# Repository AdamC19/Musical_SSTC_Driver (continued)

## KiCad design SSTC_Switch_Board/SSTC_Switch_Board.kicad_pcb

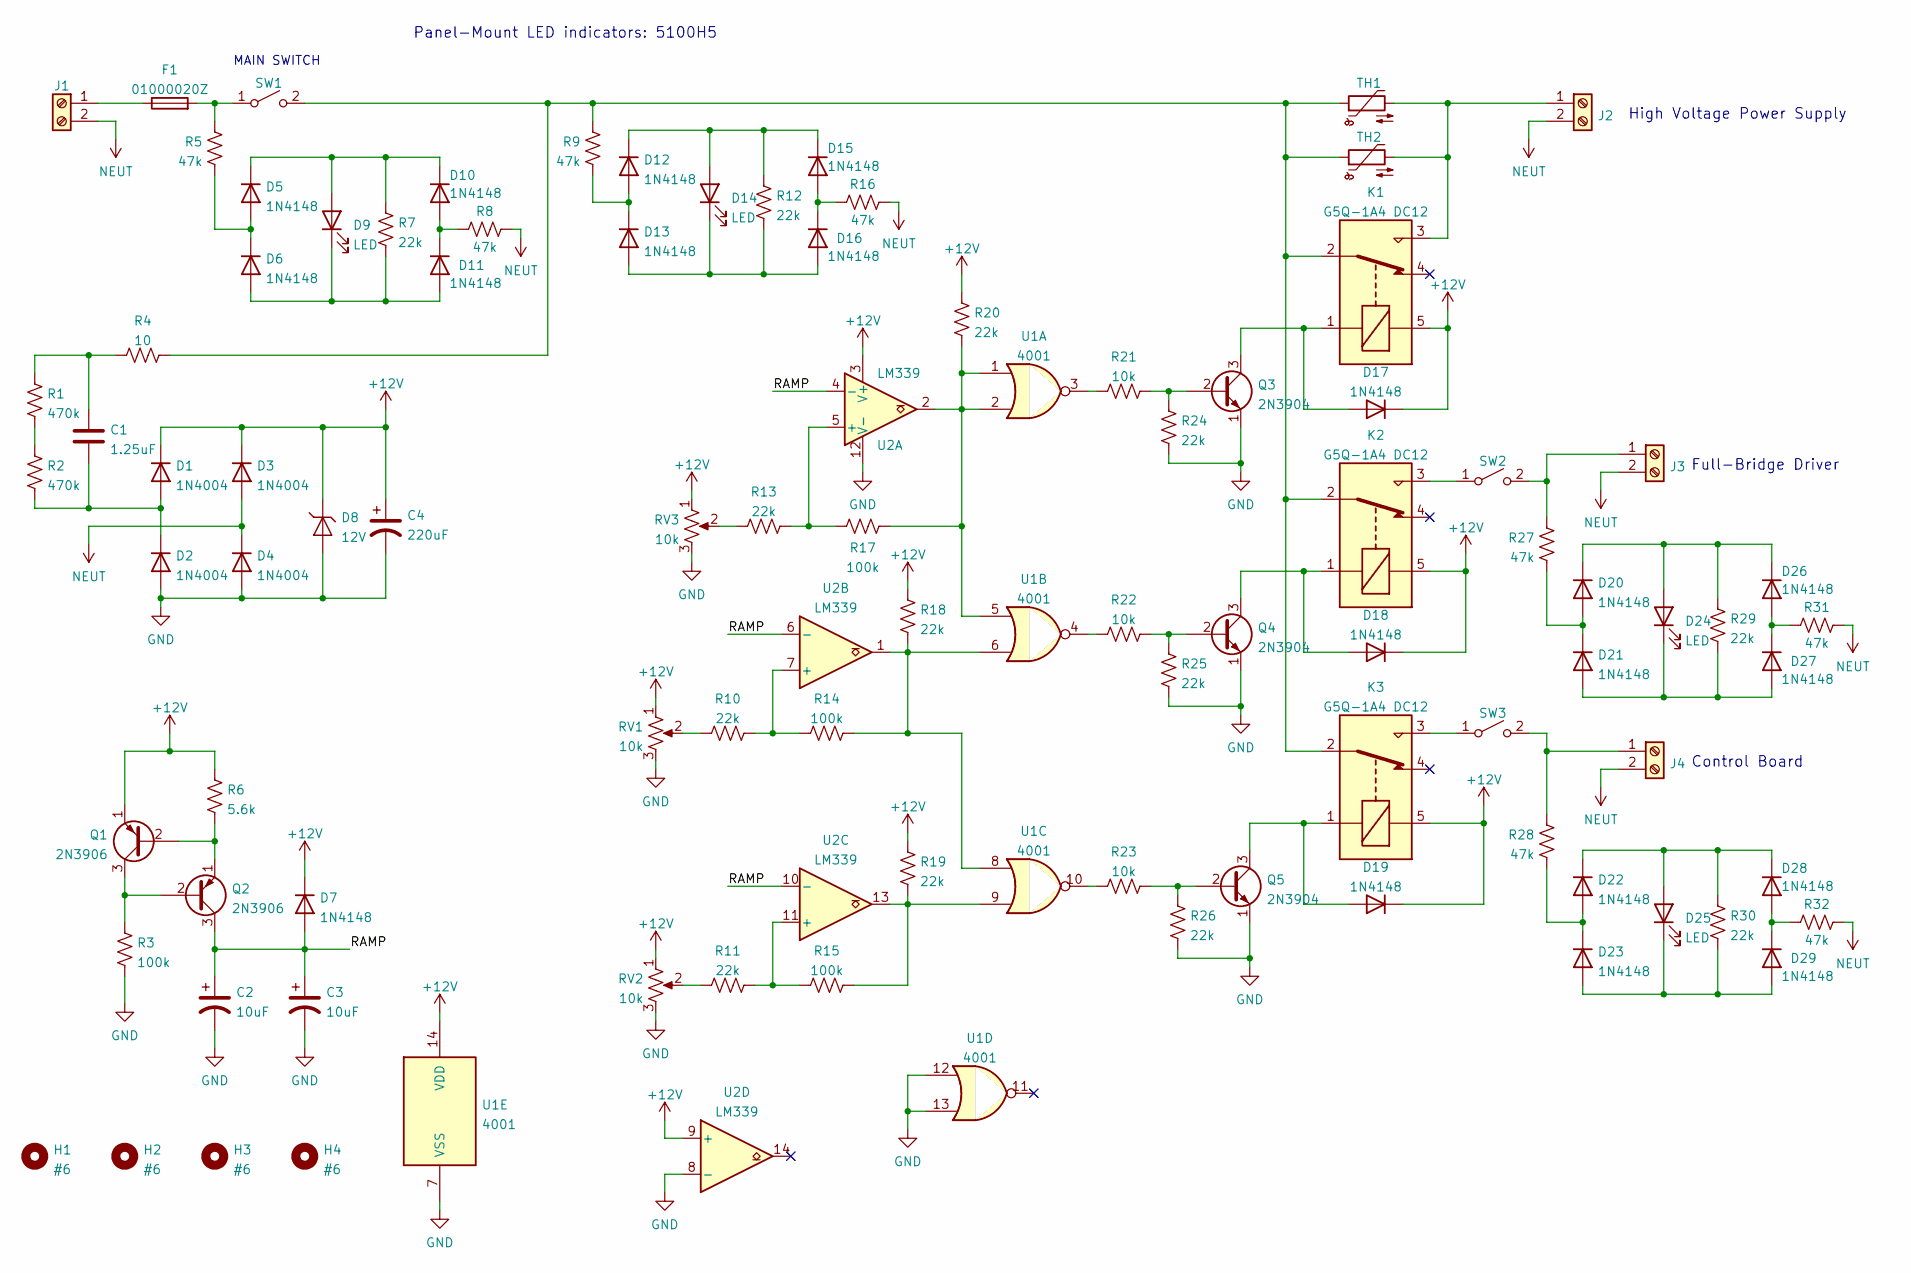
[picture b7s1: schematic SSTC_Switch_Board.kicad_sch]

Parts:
C1: 1.25uF; C_Rect_L24.0mm_W8.3mm_P22.50mm_MKT
C2, C3: 10uF; CP_Radial_D6.3mm_P2.50mm
C4: 220uF; CP_Radial_D10.0mm_P5.00mm
D1, D2, D3, D4: 1N4004; D_DO-41_SOD81_P10.16mm_Horizontal
D5, D6, D7, D10, D11, D12, D13, D15, D16, D17, D18, D19, D20, D21, D22, D23, D26, D27, D28, D29: 1N4148; D_DO-35_SOD27_P7.62mm_Horizontal
D8: 12V; D_DO-41_SOD81_P10.16mm_Horizontal
D9, D14, D24, D25: LED; JST_XH_B2B-XH-A_1x02_P2.50mm_Vertical; MFG_PN B2B-XH-A(LF)(SN)
F1: 01000020Z; Fuseholder_Littelfuse_100_series_5x20mm; MFG_PN 01000020Z
H1, H2, H3, H4: #6; MountingHole_3.7mm_Pad
J1, J2, J3, J4: Screw_Terminal_01x02; PhoenixContact_GMSTBVA_2,5_2-G-7,62_1x02_P7.62mm_Vertical
K1, K2, K3: G5Q-1A4 DC12; Relay_SPDT_Omron-G5Q-1; MFG_PN G5Q-1A4 DC12
Q1, Q2: 2N3906; TO-92_Inline_Wide
Q3, Q4, Q5: 2N3904; TO-92_Inline_Wide
R1, R2: 470k; R_Axial_DIN0207_L6.3mm_D2.5mm_P10.16mm_Horizontal
R3, R14, R15, R17: 100k; R_Axial_DIN0207_L6.3mm_D2.5mm_P10.16mm_Horizontal
R4: 10; R_Axial_DIN0414_L11.9mm_D4.5mm_P15.24mm_Horizontal
R5, R8, R9, R16, R27, R28, R31, R32: 47k; R_Axial_DIN0207_L6.3mm_D2.5mm_P10.16mm_Horizontal
R6: 5.6k; R_Axial_DIN0207_L6.3mm_D2.5mm_P10.16mm_Horizontal
R7, R10, R11, R12, R13, R18, R19, R20, R26, R29, R30: 22k; R_Axial_DIN0207_L6.3mm_D2.5mm_P10.16mm_Horizontal
R21, R22, R23: 10k; R_Axial_DIN0207_L6.3mm_D2.5mm_P10.16mm_Horizontal
R24, R25: 22k; R_Axial_DIN0207_L6.3mm_D2.5mm_P2.54mm_Vertical
RV1, RV2, RV3: 10k; Potentiometer_Bourns_3386P_Vertical
SW1, SW2, SW3: SW_SPST; PhoenixContact_GMSTBVA_2,5_2-G-7,62_1x02_P7.62mm_Vertical
TH1, TH2: B57238S0220M051; RV_Disc_D15.5mm_W5.9mm_P7.5mm; MFG_PN B57238S0220M051
U1: 4001; DIP-14_W7.62mm
U2: LM339; DIP-14_W7.62mm

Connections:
+12V: C4.1, D1.1 (K), D3.1 (K), D7.1 (K), D8.1 (K), D17.1 (K), D18.1 (K), D19.1 (K), K1.5, K2.5, K3.5, Q1.1 (E), R6.1, R18.2, R19.2, R20.2, RV1.1, RV2.1, RV3.1, U1.14 (VDD), U2.3 (V+), U2.9 (+)
/RAMP: C2.1, C3.1, D7.2 (A), Q2.3 (C), U2.4 (-), U2.6 (-), U2.10 (-)
GND: C2.2, C3.2, C4.2, D2.2 (A), D4.2 (A), D8.2 (A), Q3.1 (E), Q4.1 (E), Q5.1 (E), R3.2, R24.1, R25.1, R26.1, RV1.3, RV2.3, RV3.3, U1.7 (VSS), U1.12, U1.13, U2.8 (-), U2.12 (V-)
NEUT: D3.2 (A), D4.1 (K), J1.2, J2.2, J3.2, J4.2, R8.1, R16.1, R31.1, R32.1
unnamed: C1.1, R1.1, R4.2
unnamed: C1.2, D1.2 (A), D2.1 (K), R2.2
unnamed: D5.2 (A), D6.1 (K), R5.2
unnamed: D5.1 (K), D9.2 (A), D10.1 (K), R7.2
unnamed: D10.2 (A), D11.1 (K), R8.2
unnamed: D6.2 (A), D9.1 (K), D11.2 (A), R7.1
unnamed: D12.1 (K), D14.2 (A), D15.1 (K), R12.2
unnamed: D12.2 (A), D13.1 (K), R9.2
unnamed: D13.2 (A), D14.1 (K), D16.2 (A), R12.1
unnamed: D15.2 (A), D16.1 (K), R16.2
unnamed: D17.2 (A), K1.1, Q3.3 (C)
unnamed: D18.2 (A), K2.1, Q4.3 (C)
unnamed: D19.2 (A), K3.1, Q5.3 (C)
unnamed: D20.1 (K), D24.2 (A), D26.1 (K), R29.2
unnamed: D20.2 (A), D21.1 (K), R27.2
unnamed: D21.2 (A), D24.1 (K), D27.2 (A), R29.1
unnamed: D22.1 (K), D25.2 (A), D28.1 (K), R30.2
unnamed: D22.2 (A), D23.1 (K), R28.2
unnamed: D23.2 (A), D25.1 (K), D29.2 (A), R30.1
unnamed: D26.2 (A), D27.1 (K), R31.2
unnamed: D28.2 (A), D29.1 (K), R32.2
unnamed: F1.1, J1.1
unnamed: F1.2, R5.1, SW1.1 (A)
unnamed: J2.1, K1.3, TH1.2, TH2.2
unnamed: J3.1, R27.1, SW2.2 (B)
unnamed: J4.1, R28.1, SW3.2 (B)
unnamed: K1.2, K2.2, K3.2, R4.1, R9.1, SW1.2 (B), TH1.1, TH2.1
unnamed: K2.3, SW2.1 (A)
unnamed: K3.3, SW3.1 (A)
unnamed: Q1.2 (B), Q2.1 (E), R6.2
unnamed: Q1.3 (C), Q2.2 (B), R3.1
unnamed: Q3.2 (B), R21.2, R24.2
unnamed: Q4.2 (B), R22.2, R25.2
unnamed: Q5.2 (B), R23.2, R26.2
unnamed: R1.2, R2.1
unnamed: R10.1, RV1.2
unnamed: R10.2, R14.1, U2.7 (+)
unnamed: R11.1, RV2.2
unnamed: R11.2, R15.1, U2.11 (+)
unnamed: R13.1, RV3.2
unnamed: R13.2, R17.1, U2.5 (+)
unnamed: R14.2, R18.1, U1.6, U1.8, U2.1
unnamed: R15.2, R19.1, U1.9, U2.13
unnamed: R17.2, R20.1, U1.1, U1.2, U1.5, U2.2
unnamed: R21.1, U1.3
unnamed: R22.1, U1.4
unnamed: R23.1, U1.10

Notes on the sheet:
Panel-Mount LED indicators: 5100H5
High Voltage Power Supply
Full-Bridge Driver
MAIN SWITCH
Control Board

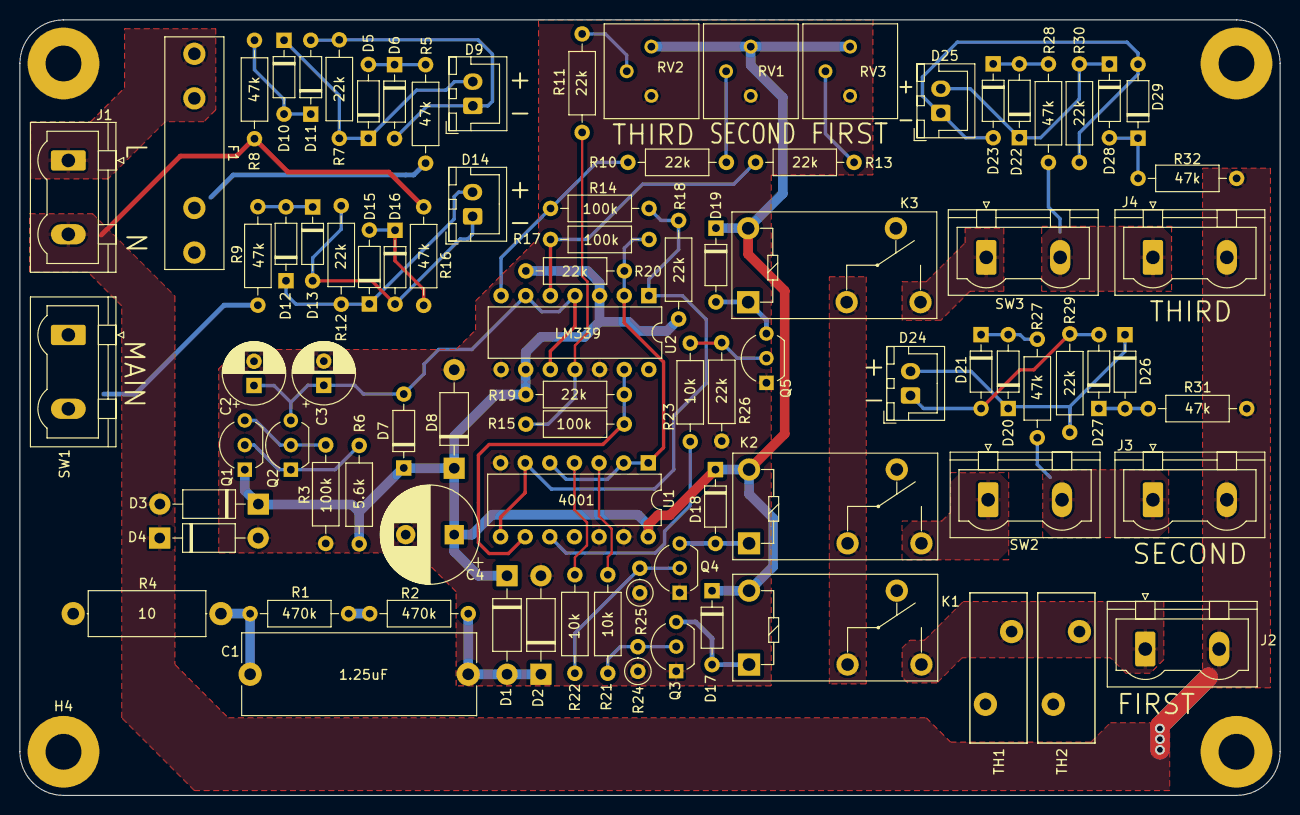
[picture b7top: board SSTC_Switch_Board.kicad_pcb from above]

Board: 2 copper layers, 130.0 x 80.0 mm, 92 parts (0 on the bottom side), 51 nets.

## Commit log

2022-02-09 Add barebones readme
2022-02-09 Add readmes and stuff
2022-02-14 Audio isolator stuff and small changes
2022-02-15 Finish Audio Isolator layout, begin routing
2022-10-14 Files sent out for fabrication
